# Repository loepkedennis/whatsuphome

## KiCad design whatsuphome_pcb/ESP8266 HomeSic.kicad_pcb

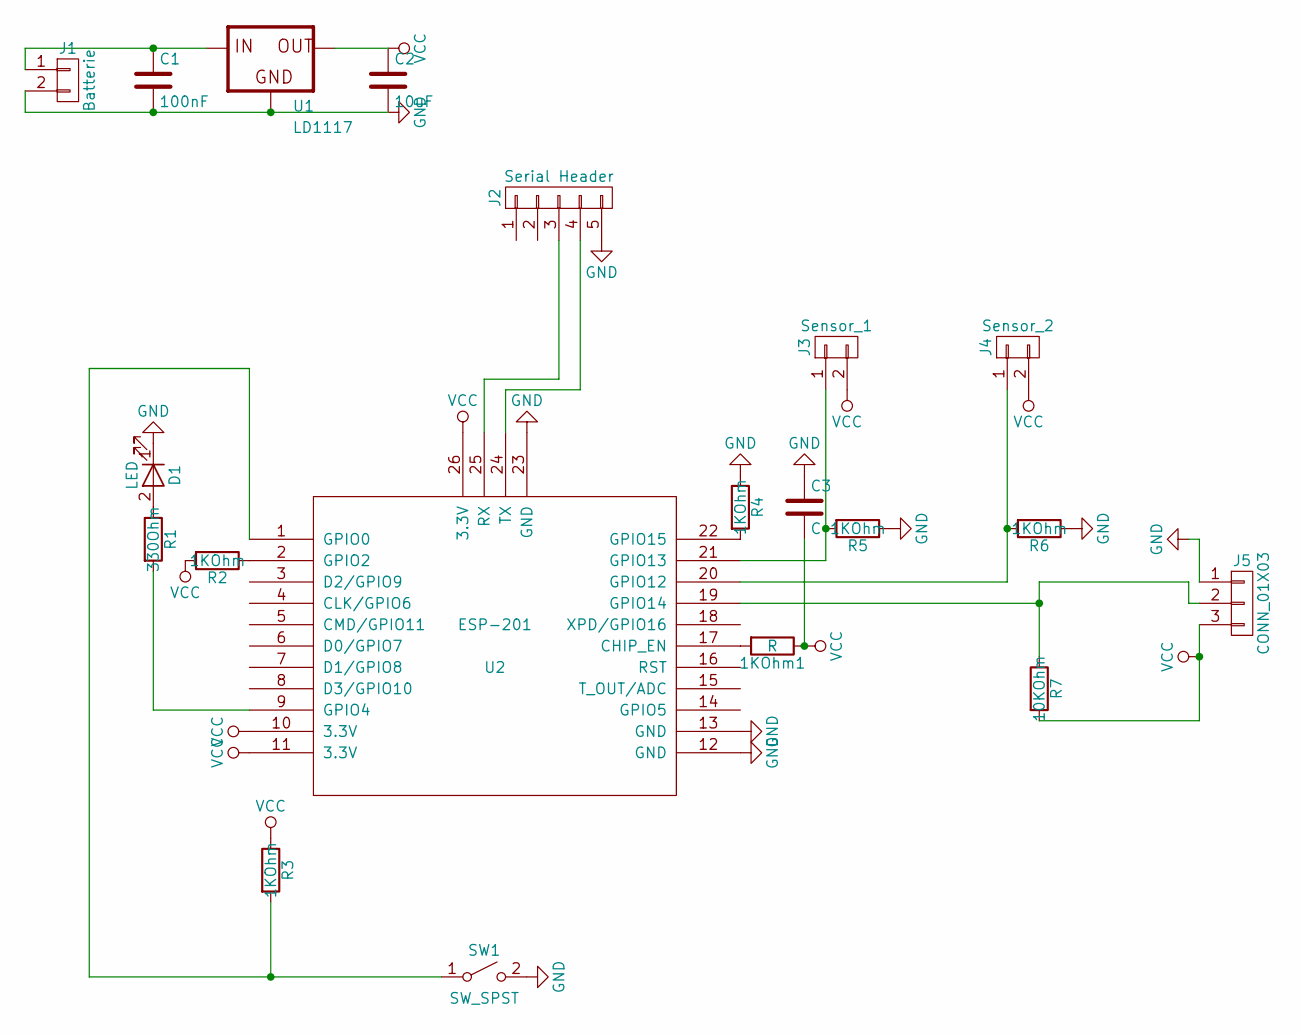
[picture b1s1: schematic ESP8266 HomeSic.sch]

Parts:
1KOhm1: R; R_Box_L8.4mm_W2.5mm_P5.08mm
C1: 100nF; C_Disc_D3.0mm_W1.6mm_P2.50mm
C2: 10uF; C_Disc_D3.0mm_W1.6mm_P2.50mm
C3: C; C_Disc_D3.0mm_W1.6mm_P2.50mm
D1: LED; LED_D3.0mm_FlatTop
J1: Batterie; Pin_Header_Straight_1x02_Pitch2.54mm
J2: Serial Header; Pin_Header_Straight_1x05_Pitch2.54mm
J3: Sensor_1; Pin_Header_Straight_1x02_Pitch2.54mm
J4: Sensor_2; Pin_Header_Straight_1x02_Pitch2.54mm
J5: CONN_01X03; Pin_Header_Straight_1x03_Pitch2.54mm
R1: 330Ohm; R_Box_L8.4mm_W2.5mm_P5.08mm
R2, R3, R4, R5, R6: 1KOhm; R_Box_L8.4mm_W2.5mm_P5.08mm
R7: 10KOhm; R_Box_L8.4mm_W2.5mm_P5.08mm
SW1: SW_SPST; SW_PUSH-12mm
U1: LD1117; TO220
U2: ESP-201

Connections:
GND: C1.2, C2.2, C3.1, D1.1 (K), J1.2, J2.5, J5.1, R4.1, R5.1, R6.1, SW1.2 (B), U1.1 (GND), U2.12 (GND), U2.13 (GND), U2.23 (GND)
unnamed: 1KOhm1.2, U2.17 (CHIP_EN)
unnamed: C1.1, J1.1, U1.3 (IN)
unnamed: D1.2 (A), R1.1
unnamed: J2.3, U2.25 (RX)
unnamed: J2.4, U2.24 (TX)
unnamed: J3.1, R5.2, U2.21 (GPIO13)
unnamed: J4.1, R6.2, U2.20 (GPIO12)
unnamed: J5.2, R7.1, U2.19 (GPIO14)
unnamed: R1.2, U2.9 (GPIO4)
unnamed: R2.1, U2.2 (GPIO2)
unnamed: R3.2, SW1.1 (A), U2.1 (GPIO0)
unnamed: R4.2, U2.22 (GPIO15)
VCC: 1KOhm1.1, C2.1, C3.2, J3.2, J4.2, J5.3, R2.2, R3.1, R7.2, U1.2 (OUT), U2.10 (3.3V), U2.11 (3.3V), U2.26 (3.3V)

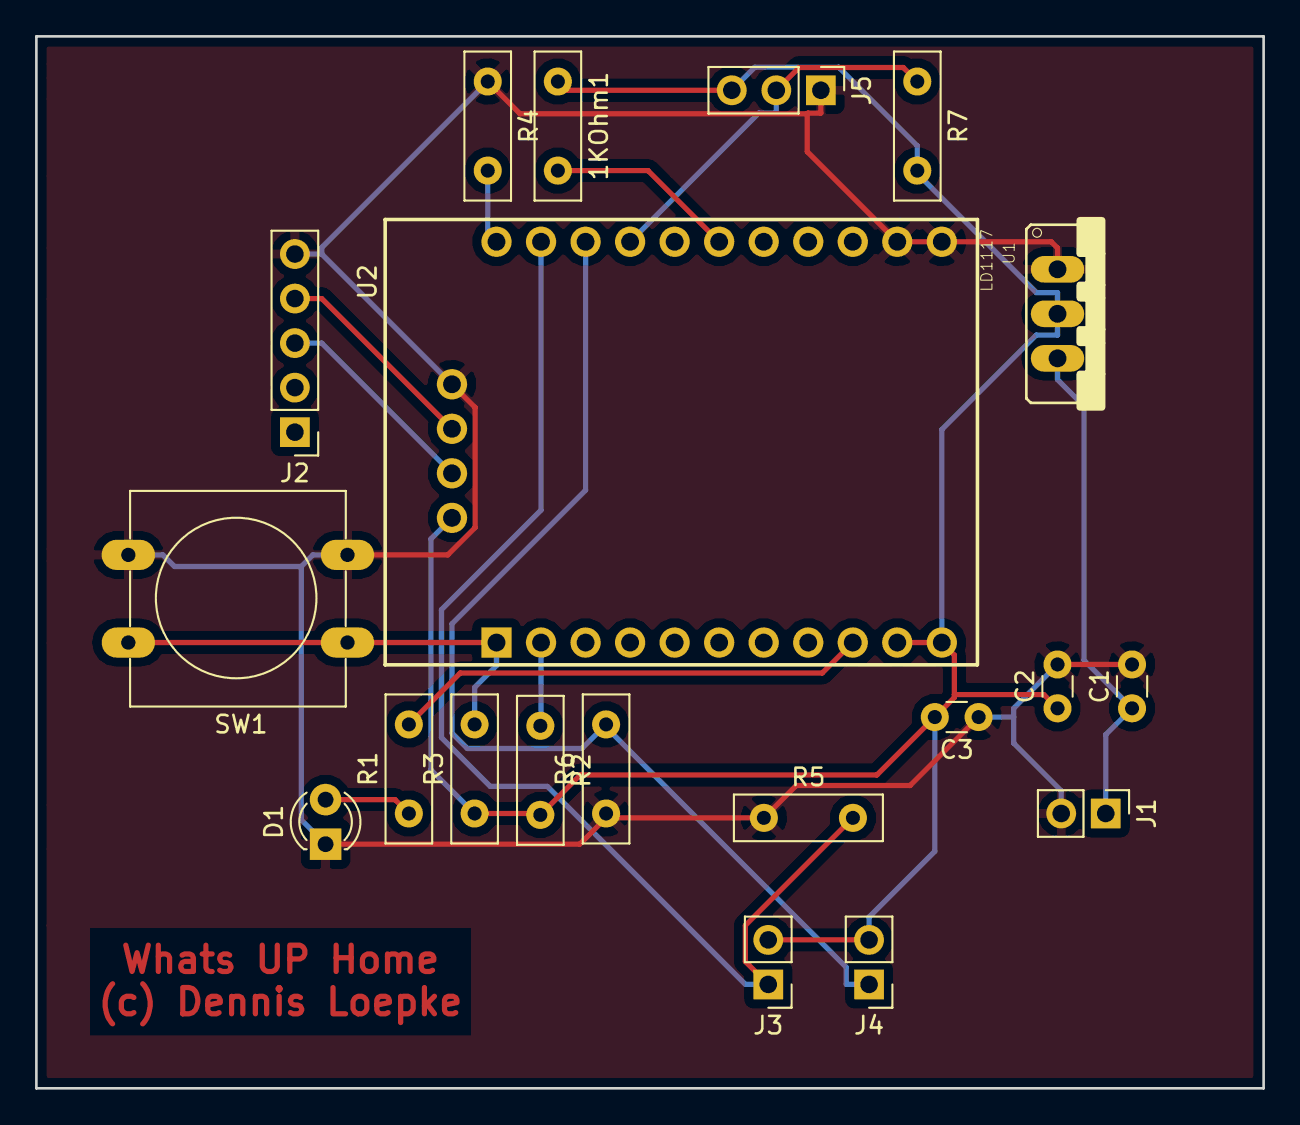
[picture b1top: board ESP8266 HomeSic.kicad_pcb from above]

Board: 2 copper layers, 70.0 x 60.0 mm, 20 parts (0 on the bottom side), 14 nets.

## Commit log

2017-07-08 init Commit
